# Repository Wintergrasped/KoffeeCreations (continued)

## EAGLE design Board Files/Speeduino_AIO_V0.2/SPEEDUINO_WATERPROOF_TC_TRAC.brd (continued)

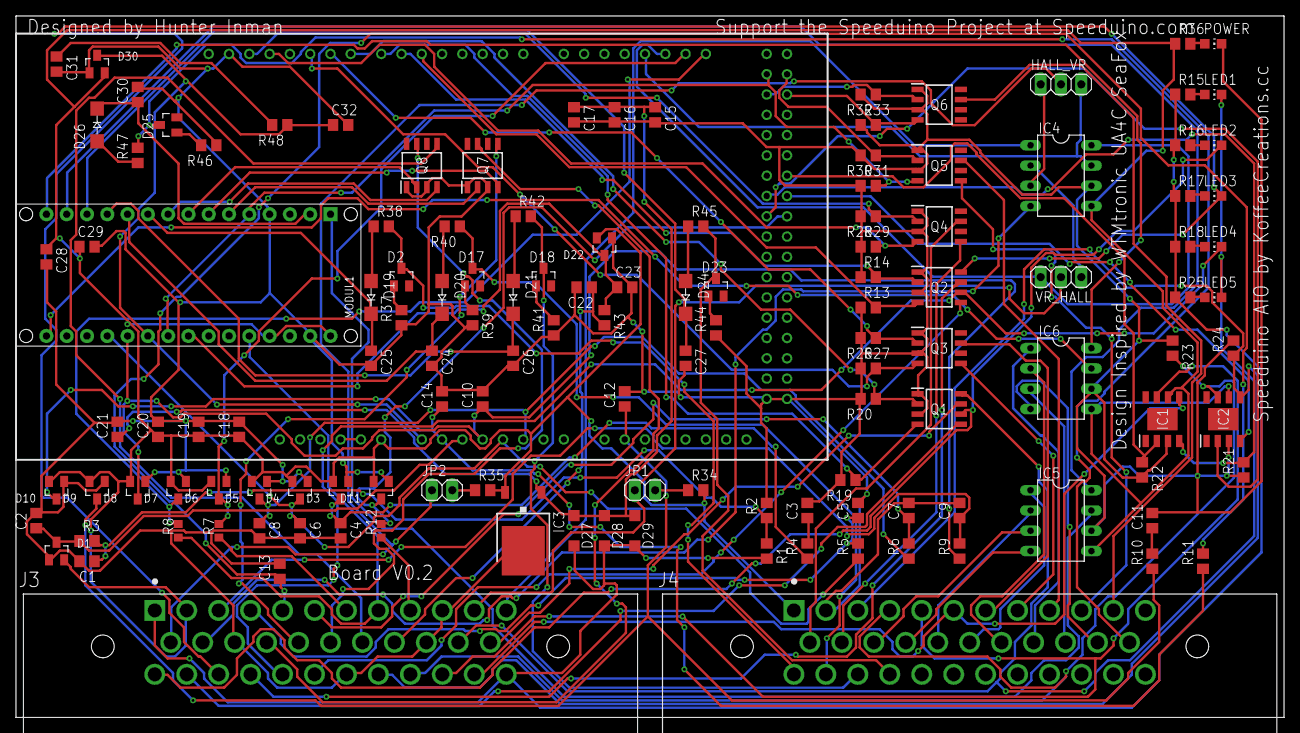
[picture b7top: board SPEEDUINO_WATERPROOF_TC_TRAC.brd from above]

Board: 2 copper layers, 158.7 x 87.8 mm, 133 parts (0 on the bottom side), 120 nets.

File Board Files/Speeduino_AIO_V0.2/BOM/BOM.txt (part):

Partlist exported from C:/Users/Wintergrasped/Documents/EAGLE/projects/Audi_ECU/SPEEDUINO_WATERPROOF_TC_TRAC.sch at 3/9/2020 7:00 PM

Qty Value         Device           Package            Parts                                                                                    Description                                                                            ANZAHL AVAILABILITY DESCRIPTION                                                                                       HEIGHT  MANUFACTURER    MANUFACTURER_NAME  MANUFACTURER_PART_NUMBER MF               MODUL MOUSER_PART_NUMBER MOUSER_PRICE-STOCK                                                  MP     PACKAGE                   PARTREV POPULARITY PRICE SPICEPREFIX STANDARD                STECKPSI0 STECKPSI1 STECKX0 STECKX1 STECKY0 STECKY1
3                 DIL8             DIL08              IC4, IC5, IC6                                                                            Dual In Line / Socket                                                                                                                                                                                                                                                                                                                                                                                                                   8                                                                                                       
3                 DIODE-SOD123     SOD123             D27, D28, D29                                                                            DIODE                                                                                                                                                                                                                                                                                                                                                                                                                                   22                                                                                                      
6                 LEDCHIP-LED0805  CHIP-LED0805       LED1, LED2, LED3, LED4, LED5, POWER                                                      LED                                                                                                                                                                                                                                                                                                                                                                                                                                     68                                                                                                      
2                 PINHD-1X2        1X02               JP1, JP2                                                                                 PIN HEADER                                                                                                                                                                                                                                                                                                                                                                                                                              98                                                                                                      
2                 PINHD-1X3        1X03               HALL_VR, VR_HALL                                                                         PIN HEADER                                                                                                                                                                                                                                                                                                                                                                                                                              92                                                                                                      
5                 ZENER-DIODESOT23 SOT23              D2, D17, D18, D23, D25                                                                   Z-Diode                                                                                                                                                                                                                                                                                                                                                                                                                                 3                                                                                                       
17  100K          R-US_R0805       R0805              R13, R14, R19, R21, R22, R23, R24, R26, R27, R28, R29, R30, R31, R32, R33, R34, R35      RESISTOR, American symbol                                                                                                                                                                                                                                                                                                                                                                                                               85               R                                                                                      
1   100k          R-US_R0805       R0805              R20                                                                                      RESISTOR, American symbol                                                                                                                                                                                                                                                                                                                                                                                                               85               R                                                                                      
1   1K            R-US_R0805       R0805              R2                                                                                       RESISTOR, American symbol                                                                                                                                                                                                                                                                                                                                                                                                               85               R                                                                                      
6   2K            R-US_R0805       R0805              R15, R16, R17, R18, R25, R36                                                             RESISTOR, American symbol                                                                                                                                                                                                                                                                                                                                                                                                               85               R                                                                                      
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
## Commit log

2020-03-28 Update TransControllerFirmware.ino
    Added Error catching and reporting
2020-03-28 Added Traction Control Module files
2020-04-16 Added ECU Switcher files
2020-05-23 Add Window Controller
    Added Electric window control board files.
2020-05-23 Added IDC40 to AMPSEAL adapter
    Added board files for IDC40 to AMPSEAL adapter.
2022-04-16 Updated Firmwares
